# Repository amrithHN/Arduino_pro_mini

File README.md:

# Arduino_pro_mini
## Arduino pro mini

built using KiCAD 6

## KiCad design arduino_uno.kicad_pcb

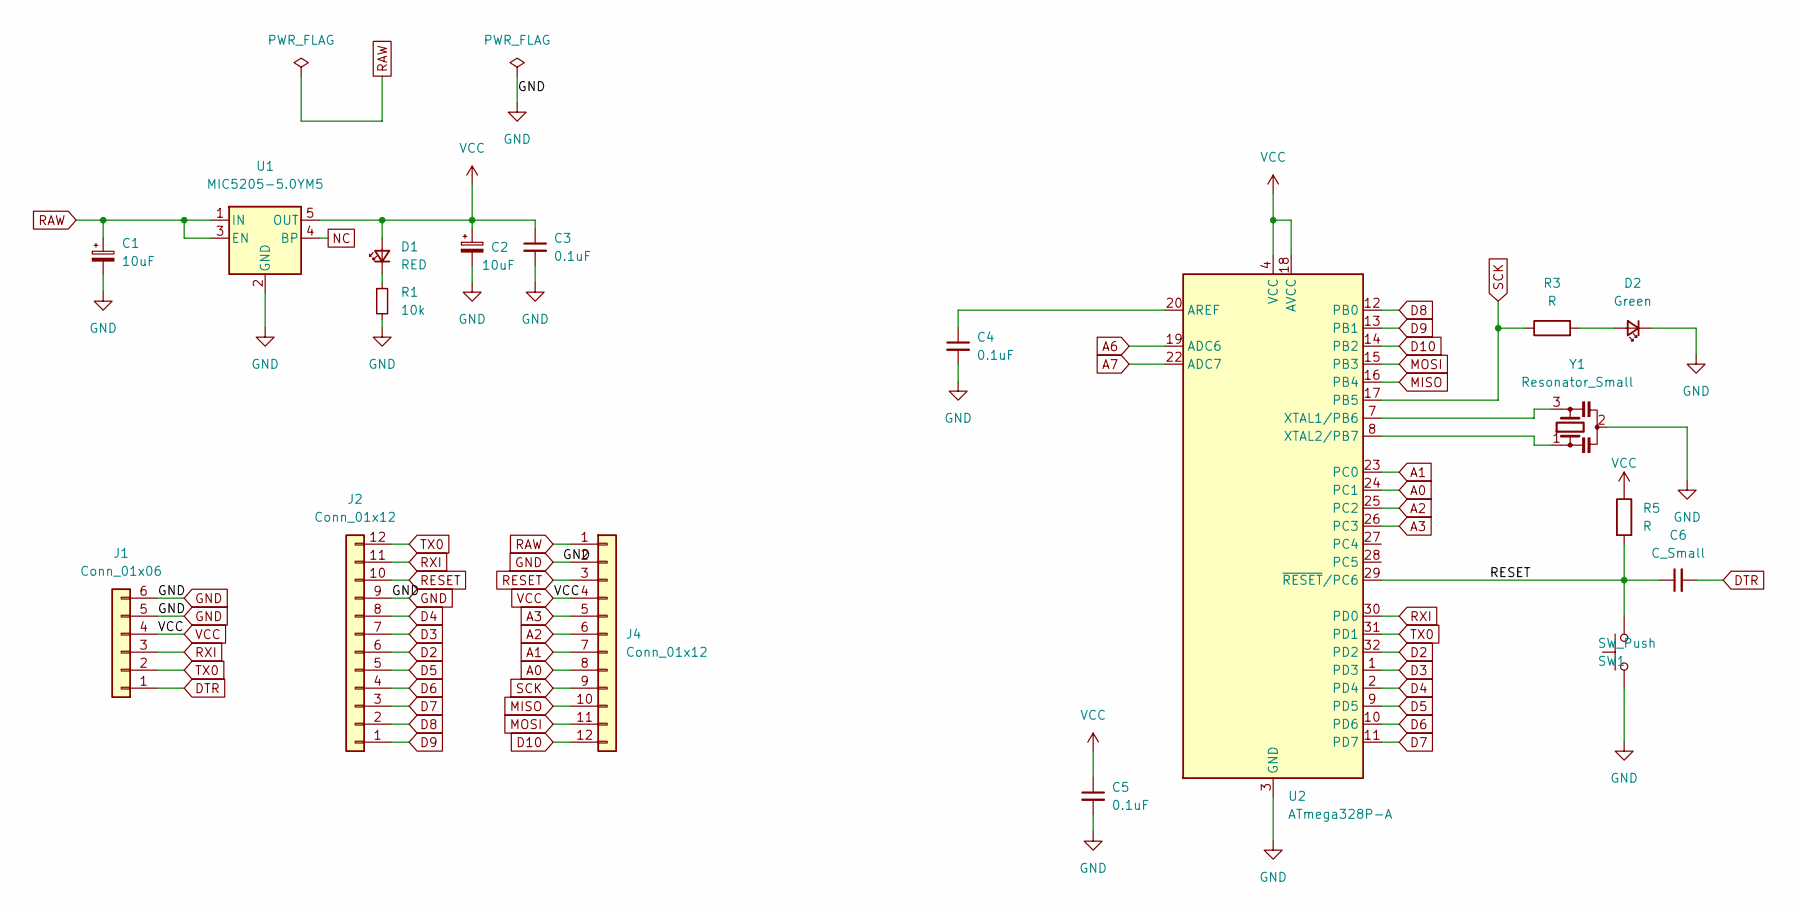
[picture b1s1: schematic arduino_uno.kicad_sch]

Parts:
C1, C2: 10uF; C_0603_1608Metric
C3, C4, C5: 0.1uF; C_0603_1608Metric
C6: C_Small; C_0603_1608Metric
D1: RED; LED_0603_1608Metric
D2: Green; LED_0603_1608Metric
J1: Conn_01x06; PinHeader_1x06_P2.54mm_Vertical
J2, J4: Conn_01x12; PinHeader_1x12_P2.54mm_Vertical
R1: 10k; R_0603_1608Metric
R3, R5: R; R_0603_1608Metric
SW1: SW_Push; SW_SOV-168HST
U1: MIC5205-5.0YM5; SOT-23-5
U2: ATmega328P-A; TQFP-32_7x7mm_P0.8mm
Y1: Resonator_Small; OSC_CSTNE16M0V51Z000R0

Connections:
A0: J4.8, U2.24 (PC1)
A1: J4.7, U2.23 (PC0)
A2: J4.6, U2.25 (PC2)
A3: J4.5, U2.26 (PC3)
A6: U2.19 (ADC6)
A7: U2.22 (ADC7)
D2: J2.6, U2.32 (PD2)
D3: J2.7, U2.1 (PD3)
D4: J2.8, U2.2 (PD4)
D5: J2.5, U2.9 (PD5)
D6: J2.4, U2.10 (PD6)
D7: J2.3, U2.11 (PD7)
D8: J2.2, U2.12 (PB0)
D9: J2.1, U2.13 (PB1)
D10: J4.12, U2.14 (PB2)
DTR: C6.2, J1.1
GND: C1.2, C2.2, C3.2, C4.2, C5.2, D2.1 (K), J1.5, J1.6, J2.9, J4.2, R1.2, SW1.A1, U1.2 (GND), U2.3 (GND), U2.5 (GND), U2.21 (GND), Y1.2
MISO: J4.10, U2.16 (PB4)
MOSI: J4.11, U2.15 (PB3)
NC: U1.4 (BP)
unnamed: C4.1, U2.20 (AREF)
unnamed: D1.1 (K), R1.1
unnamed: D2.2 (A), R3.2
unnamed: U2.7 (XTAL1/PB6), Y1.3
unnamed: U2.8 (XTAL2/PB7), Y1.1
RAW: C1.1, J4.1, U1.1 (IN), U1.3 (EN)
RESET: C6.1, J2.10, J4.3, R5.2, SW1.B1, U2.29 (~RESET/PC6)
RXI: J1.3, J2.11, U2.30 (PD0)
SCK: J4.9, R3.1, U2.17 (PB5)
TX0: J1.2, J2.12, U2.31 (PD1)
VCC: C2.1, C3.1, C5.1, D1.2 (A), J1.4, J4.4, R5.1, U1.5 (OUT), U2.4 (VCC), U2.6 (VCC), U2.18 (AVCC)

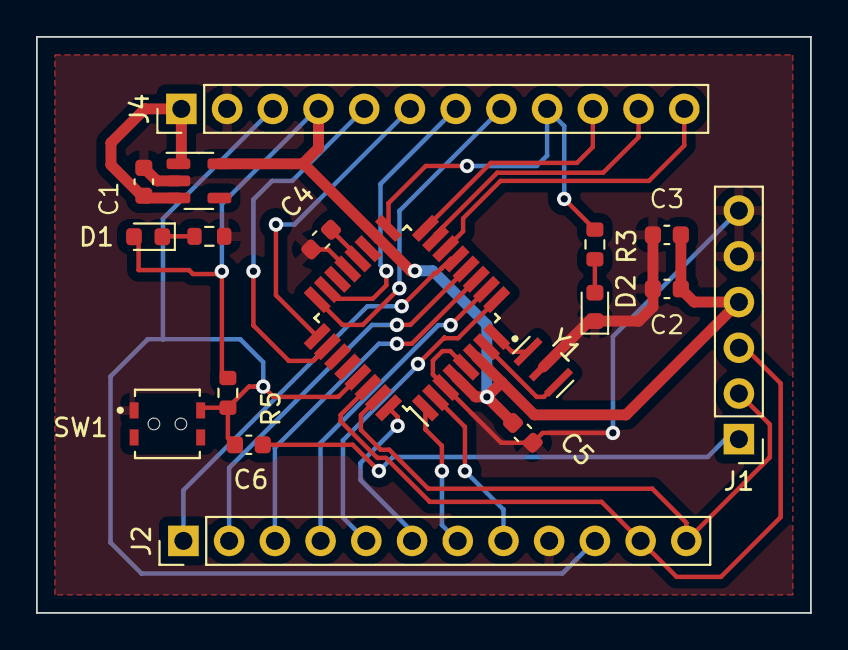
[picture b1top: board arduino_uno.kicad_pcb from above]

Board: 2 copper layers, 43.0 x 32.0 mm, 18 parts (0 on the bottom side), 28 nets.

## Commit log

2022-05-20 second commit
2022-05-20 added pics commit
2022-06-16 fix some stuff
2022-06-16 added screenshot
2022-06-16 oops
